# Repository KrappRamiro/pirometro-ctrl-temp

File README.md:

# Control de Temperatura (Pirómetro)

Para los que no usen kicad, solamente les interesan estos archivos:

## esquematico.pdf
Tiene el esquematico del proyecto

## placa_cobre.pdf
Tiene la parte que va planchada al cobre

## silkscreen.pdf

Tiene la parte que va en el frente, o sea, donde va los componentes.
Eso vos lo planchas y despues a la hora de colocar los componentes,
te ayuda a saber cuál es cual.

## placa_3D.png

Tiene una vista 3D de la placa, esta lindo :)

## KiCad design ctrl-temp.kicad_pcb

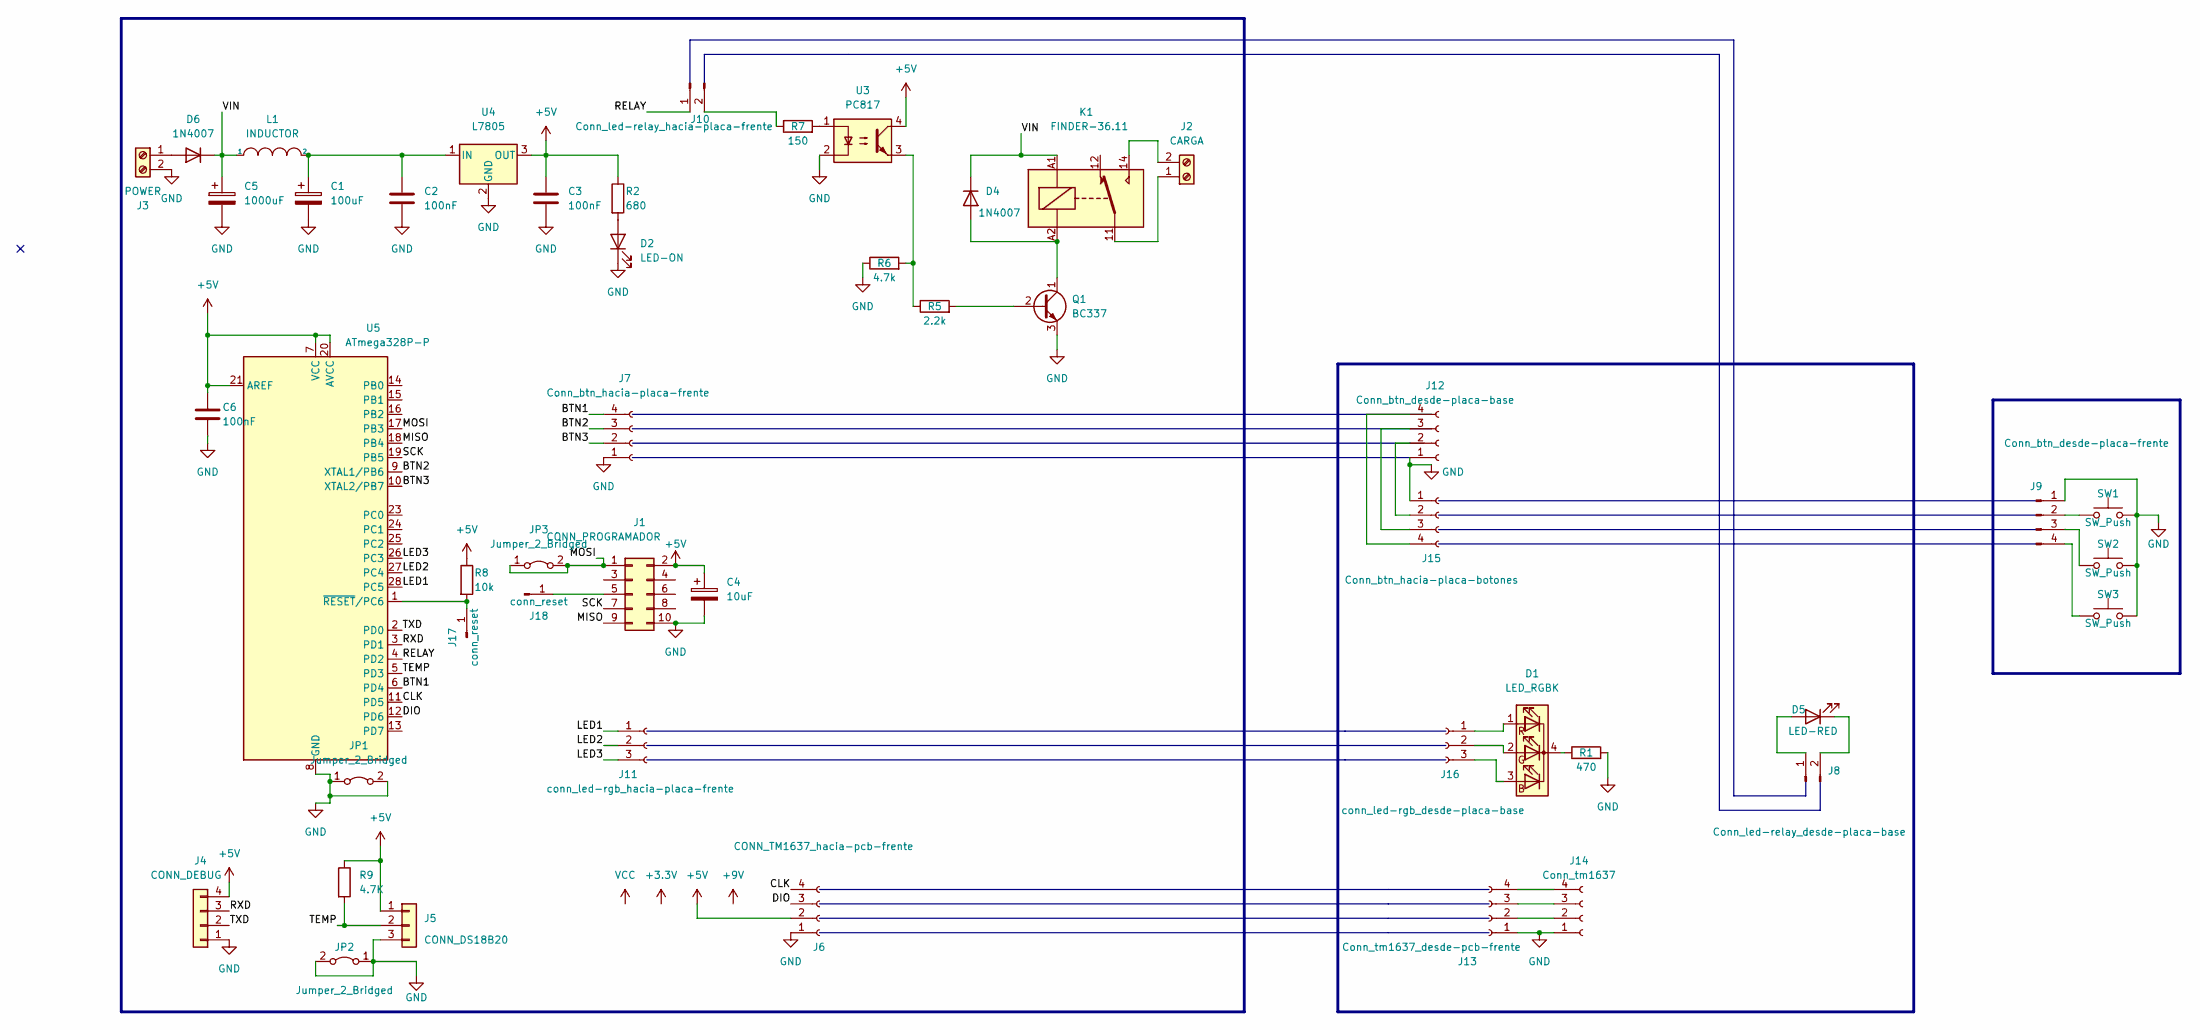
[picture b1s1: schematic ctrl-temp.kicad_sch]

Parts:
C1: 100uF; CP_Radial_D8.0mm_P5.00mm
C2, C3, C6: 100nF; C_Disc_D5.0mm_W2.5mm_P2.50mm
C4: 10uF; CP_Radial_D5.0mm_P2.50mm
C5: 1000uF; CP_Radial_D13.0mm_P5.00mm
D1: LED_RGBK; LED_D5.0mm-4_RGB
D2: LED-ON; LED_D2.0mm_W4.8mm_H2.5mm_FlatTop
D4, D6: 1N4007; D_DO-41_SOD81_P10.16mm_Horizontal
D5: LED-RED; LED_D5.0mm
J1: CONN_PROGRAMADOR; PinHeader_2x05_P2.54mm_Vertical
J2: CARGA; tblock_2x1
J3: POWER; tblock_2x1
J4: CONN_DEBUG; PinHeader_1x04_P2.54mm_Vertical
J5: CONN_DS18B20; PinHeader_1x03_P2.54mm_Vertical
J6: CONN_TM1637_hacia-pcb-frente; PinHeader_1x04_P2.54mm_Vertical
J7: Conn_btn_hacia-placa-frente; PinHeader_1x04_P2.54mm_Vertical
J8: Conn_led-relay_desde-placa-base; PinHeader_1x02_P2.54mm_Vertical
J9: Conn_btn_desde-placa-frente; PinHeader_1x04_P2.54mm_Vertical
J10: Conn_led-relay_hacia-placa-frente; PinHeader_1x02_P2.54mm_Vertical
J11: conn_led-rgb_hacia-placa-frente; PinHeader_1x03_P2.54mm_Vertical
J12: Conn_btn_desde-placa-base; PinHeader_1x04_P2.54mm_Vertical
J13: Conn_tm1637_desde-pcb-frente; PinHeader_1x04_P2.54mm_Vertical
J14: Conn_tm1637; PinSocket_1x04_P2.54mm_Vertical
J15: Conn_btn_hacia-placa-botones; PinSocket_1x04_P2.54mm_Vertical
J16: conn_led-rgb_desde-placa-base; PinHeader_1x03_P2.54mm_Vertical
J17, J18: conn_reset; PinHeader_1x01_P2.54mm_Vertical
JP1, JP2: Jumper_2_Bridged; TestPoint_Bridge_Pitch5.08mm_Drill1.3mm
JP3: Jumper_2_Bridged; TestPoint_Bridge_Pitch6.35mm_Drill1.3mm
K1: FINDER-36.11; Relay_SPDT_Finder_36.11
L1: INDUCTOR; krapp-res-generic
Q1: BC337; krapp-TO-92_HandSolder
R1: 470; krapp-res-generic
R2: 680; krapp-res-generic
R5: 2.2k; krapp-res-generic
R6: 4.7k; krapp-res-generic
R7: 150; krapp-res-generic
R8: 10k; krapp-res-generic
R9: 4.7K; krapp-res-generic
SW1, SW2, SW3: SW_Push; SW_PUSH_6mm
U3: PC817; DIP-4_W7.62mm
U4: L7805; TO-220-3_Vertical-pads-grandes
U5: ATmega328P-P; DIP-28_W7.62mm_Socket_LongPads

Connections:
+5V: C3.1, C4.1, C6.2, J1.2, J4.4, J5.1, J6.2, R2.1, R8.1, R9.1, U3.4, U4.3 (OUT), U5.7 (VCC), U5.20 (AVCC), U5.21 (AREF)
/BTN1: J7.4, U5.6 (PD4)
/BTN2: J7.3, U5.9 (XTAL1/PB6)
/BTN3: J7.2, U5.10 (XTAL2/PB7)
/CLK: J6.4, U5.11 (PD5)
/DIO: J6.3, U5.12 (PD6)
/LED1: J11.1, U5.28 (PC5)
/LED2: J11.2, U5.27 (PC4)
/LED3: J11.3, U5.26 (PC3)
/MISO: J1.9, U5.18 (PB4)
/MOSI: J1.1, JP3.1 (A), JP3.2 (B), U5.17 (PB3)
/RELAY: J10.1, U5.4 (PD2)
/RXD: J4.3, U5.3 (PD1)
/SCK: J1.7, U5.19 (PB5)
/TEMP: J5.2, R9.2, U5.5 (PD3)
/TXD: J4.2, U5.2 (PD0)
/VIN: C5.1, D4.1 (K), D6.1 (K), K1.A1, L1.1
GND: C1.2, C2.2, C3.2, C4.2, C5.2, C6.1, D2.1 (K), J1.10, J3.2, J4.1, J5.3, J6.1, J7.1, J9.1, J12.1, J13.1, J14.1, J15.1, JP1.1 (A), JP1.2 (B), JP2.1 (A), JP2.2 (B), Q1.3 (E), R1.2, R6.1, SW1.2, SW2.2, SW3.2, U3.2, U4.2 (GND), U5.8 (GND), U5.22 (GND)
unnamed: C1.1, C2.1, L1.2, U4.1 (IN)
unnamed: D1.1 (RA), J16.1
unnamed: D1.2 (GA), J16.2
unnamed: D1.3 (BA), J16.3
unnamed: D1.4 (K), R1.1
unnamed: D2.2 (A), R2.2
unnamed: D4.2 (A), K1.A2, Q1.1 (C)
unnamed: D5.1 (K), J8.2
unnamed: D5.2 (A), J8.1
unnamed: D6.2 (A), J3.1
unnamed: J1.5, J18.1
unnamed: J9.2, SW1.1
unnamed: J9.3, SW2.1
unnamed: J9.4, SW3.1
unnamed: J10.2, R7.1
unnamed: J12.2, J15.2
unnamed: J12.3, J15.3
unnamed: J12.4, J15.4
unnamed: J13.2, J14.2
unnamed: J13.3, J14.3
unnamed: J13.4, J14.4
unnamed: J2.1, K1.11
unnamed: J2.2, K1.14
unnamed: Q1.2 (B), R5.2
unnamed: R5.1, R6.2, U3.3
unnamed: R7.2, U3.1
unnamed: J17.1, R8.2, U5.1 (~RESET/PC6)

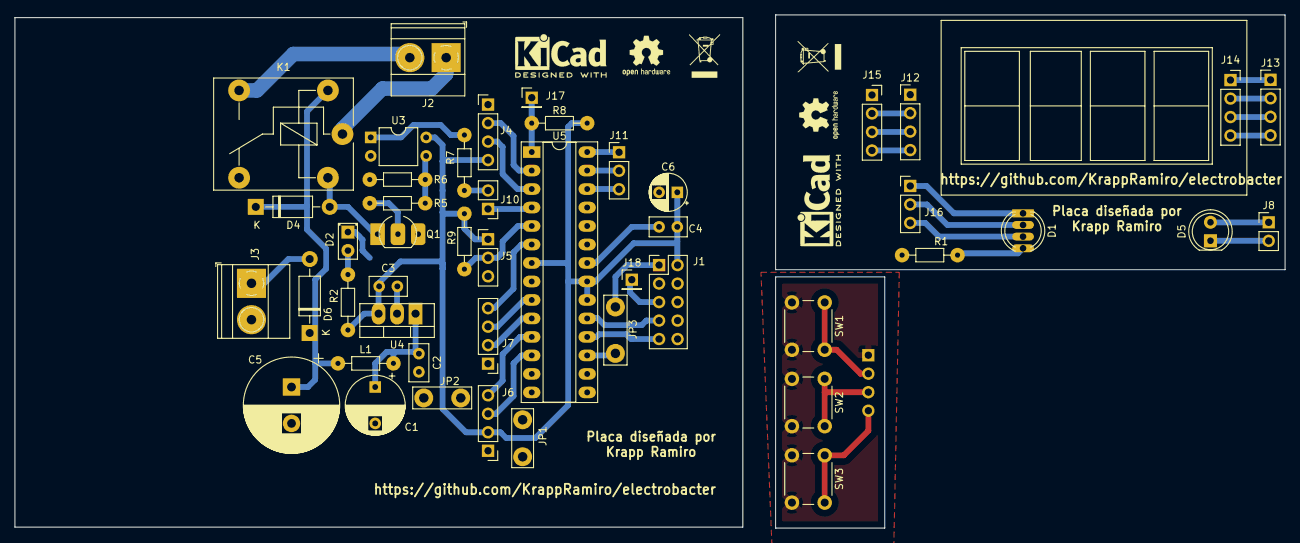
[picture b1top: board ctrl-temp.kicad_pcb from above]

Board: 2 copper layers, 174.5 x 70.5 mm, 48 parts (1 on the bottom side), 45 nets.

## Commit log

2022-05-26 hecha la placa
2022-05-27 añadido archivo para imprimir
